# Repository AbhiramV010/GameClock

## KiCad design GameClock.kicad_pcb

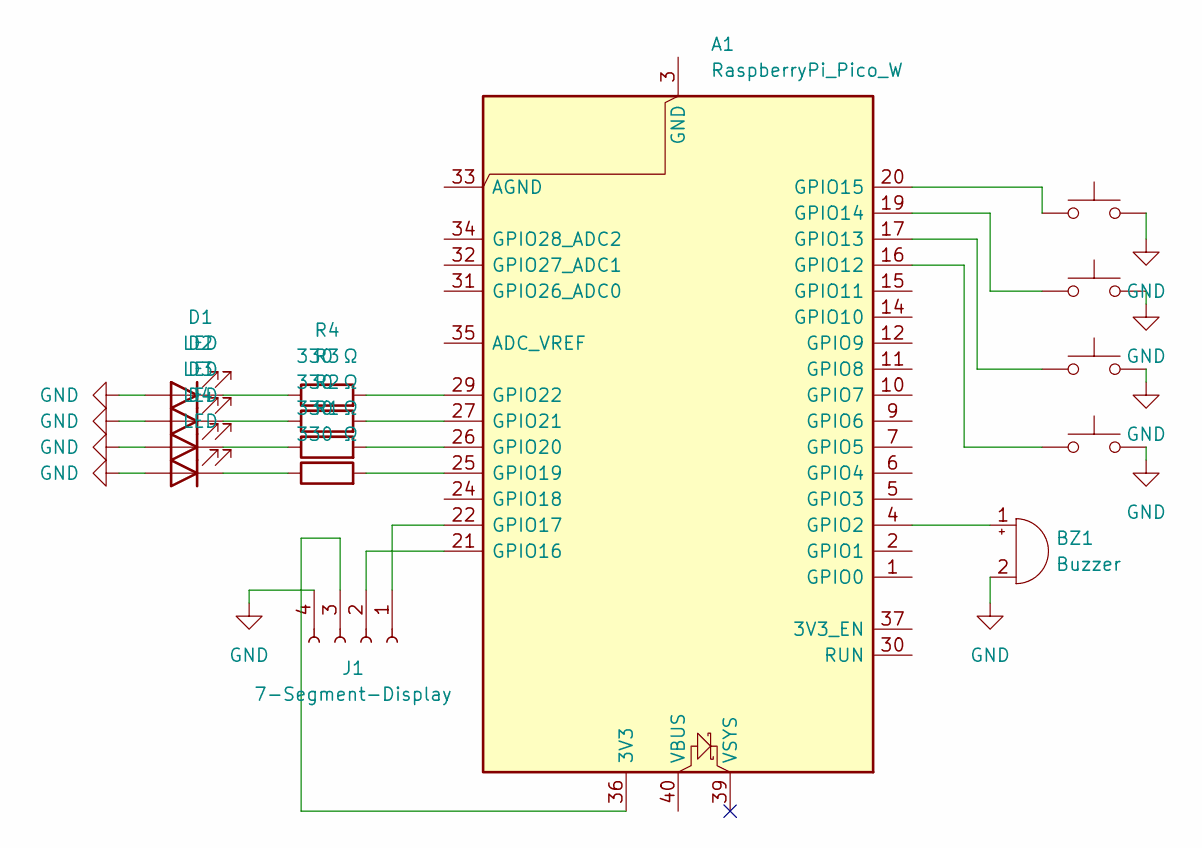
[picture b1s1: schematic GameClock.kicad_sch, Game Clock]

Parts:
A1: RaspberryPi_Pico_W; RaspberryPi_Pico_W_SMD_HandSolder
BZ1: Buzzer; Buzzer_12x9.5RM7.6
D1, D2, D3, D4: LED; LED_D2.0mm_W4.0mm_H2.8mm_FlatTop
J1: 7-Segment-Display; PinHeader_1x04_P2.54mm_Vertical
R1, R2, R3, R4: 330 Ω; R_Axial_DIN0207_L6.3mm_D2.5mm_P7.62mm_Horizontal
SW1, SW2, SW3, SW4: SW_Push; SW_PUSH_6mm

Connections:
GND: BZ1.2 (-), D1.2 (A), D2.2 (A), D3.2 (A), D4.2 (A), J1.4, SW1.2, SW2.2, SW3.2, SW4.2
unnamed: A1.36 (3V3), J1.3
unnamed: A1.3 (GND), A1.8 (GND), A1.13 (GND), A1.18 (GND), A1.23 (GND), A1.28 (GND), A1.38 (GND)
unnamed: A1.4 (GPIO2), BZ1.1 (+)
unnamed: A1.16 (GPIO12), SW4.1
unnamed: A1.17 (GPIO13), SW3.1
unnamed: A1.19 (GPIO14), SW2.1
unnamed: A1.20 (GPIO15), SW1.1
unnamed: A1.21 (GPIO16), J1.2
unnamed: A1.22 (GPIO17), J1.1
unnamed: A1.25 (GPIO19), R1.2
unnamed: A1.26 (GPIO20), R2.2
unnamed: A1.27 (GPIO21), R3.2
unnamed: A1.29 (GPIO22), R4.2
unnamed: D1.1 (K), R4.1
unnamed: D2.1 (K), R3.1
unnamed: D3.1 (K), R2.1
unnamed: D4.1 (K), R1.1

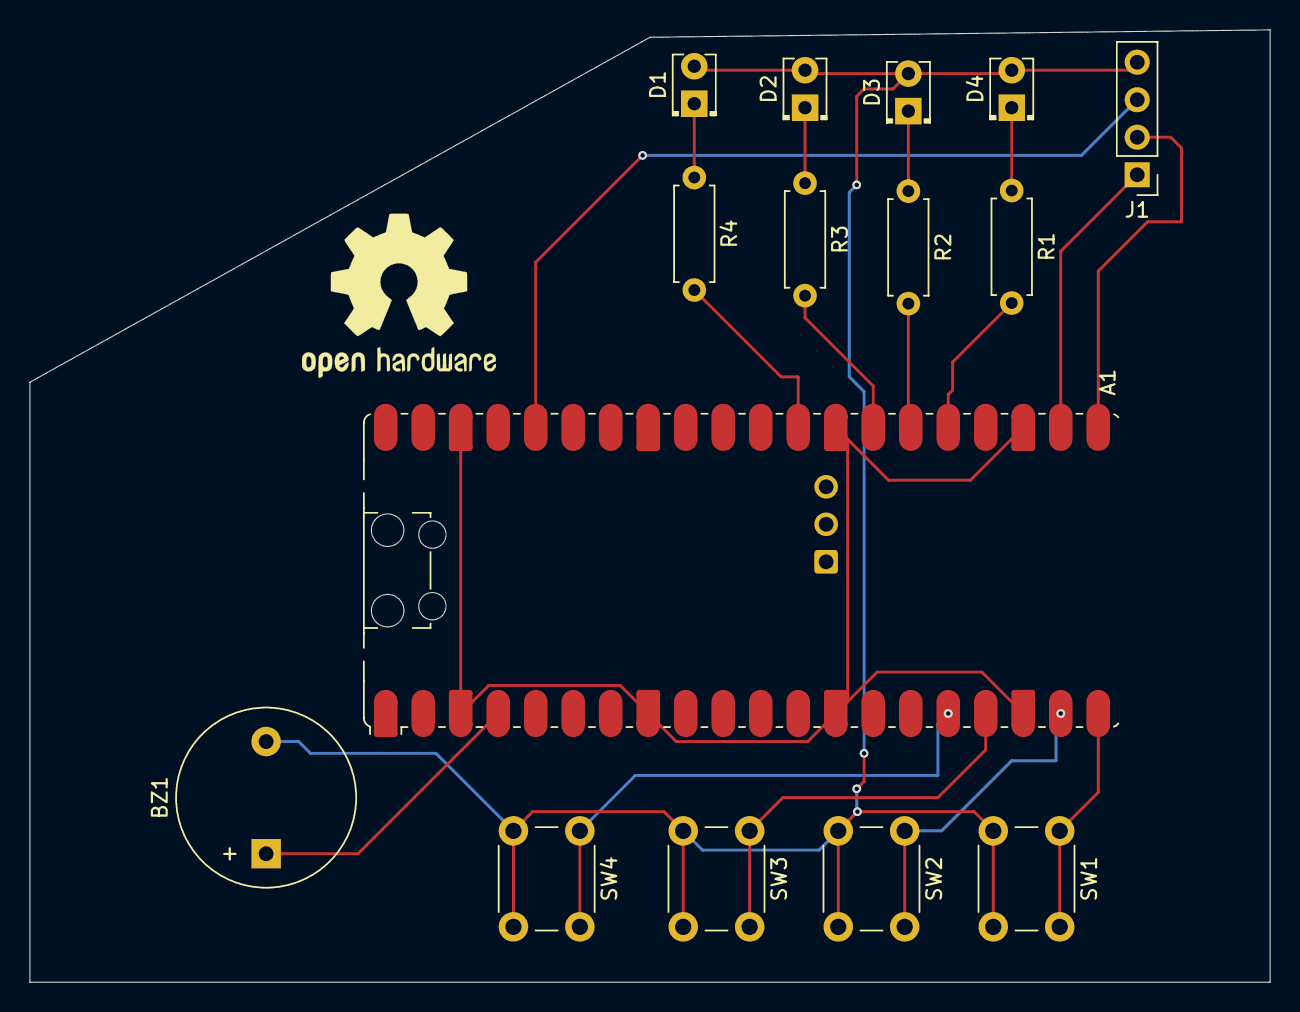
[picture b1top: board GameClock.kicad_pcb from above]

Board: 2 copper layers, 84.0 x 64.5 mm, 15 parts (0 on the bottom side), 18 nets.

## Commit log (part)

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2026-05-17 Added circuit files
2026-05-17 added labelling
